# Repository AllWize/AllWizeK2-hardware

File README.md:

# AllWize K2

The AllWize K2 is an Arduino(TM) MKR compatible board based on the SAMD21G microchip and a RadioCrafts RC1701HP module.

Resources:

* [AllWize K2 Wiki Page](http://wiki.allwize.io/index.php?title=Allwize_K2)
* [AllWize Boards](https://github.com/AllWize/allwize-boards) to support the AllWize K2 board from the Arduino IDE and PlatformIO
* [AllWize Library](https://github.com/AllWize/allwize) that supports the RC1701HP radio module.

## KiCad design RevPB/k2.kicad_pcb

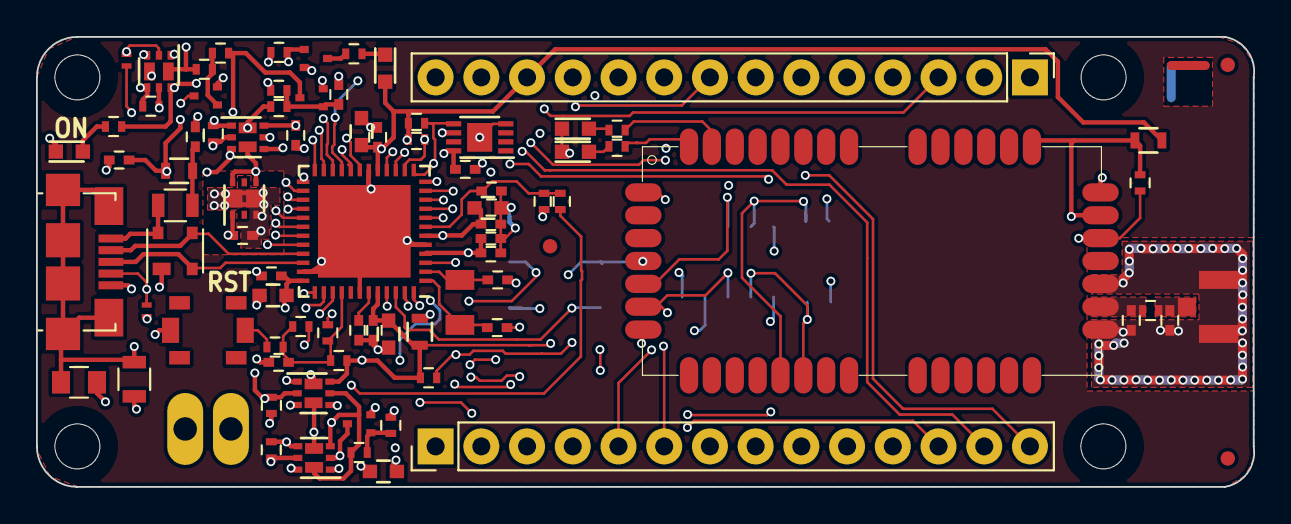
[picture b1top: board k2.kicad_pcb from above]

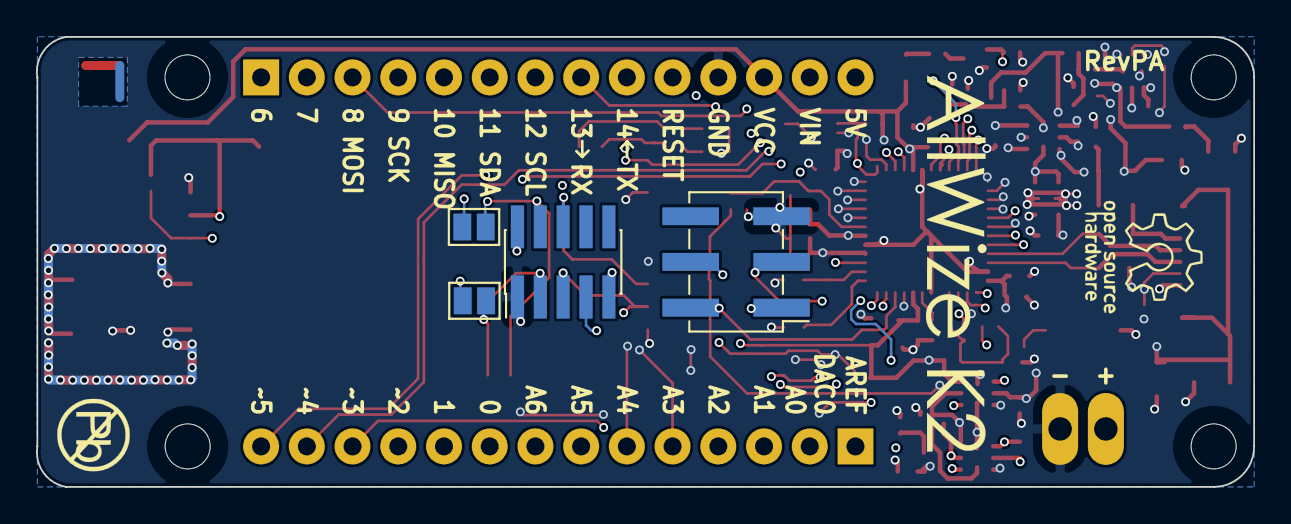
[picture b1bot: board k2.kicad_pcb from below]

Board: 4 copper layers, 67.6 x 25.0 mm, 96 parts (7 on the bottom side), 75 nets.

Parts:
C1: 4n7; C_0805
C2: 10n; C_0402
C3, C4, C5, C8, C9, C10, C16, C17, C20, C21: 100n; C_0402
C6: 4u7; C_0402
C7, C15, C19, C22, C23: 10u; C_0603
C11, C12: 20p; C_0402
C13, C14, C18: 1u; C_0402
C24, C25: 12p; C_0402
D1, D2, D5, D7: LED-DIODE; LED_0603
D3: PRTR5V0U2X; SOT-143
D4, D6: PMEG2005EL; SOD-882
FD1, FD2, FD3: FIDUCIAL; FIDUCIAL-08
G1: LOGO; allwize-k2-logo
G3: OSH; osh
G4: PB_FREE; Pb-free
J1: USB_B_Micro; USB_Micro-B_ZX62-AB-5PA_31
J2: Conn_01x02; OSTVN02
J3: Conn_02x05_Odd_Even; PinHeader_2x05_P1.27mm_Vertical_SMD
J4: Conn_Coaxial_uFL; uFL-CONN
J5: Conn_02x03_Odd_Even; PinHeader_2x03_P2.54mm_Vertical_SMD
J6, J7: Conn_01x14; PinHeader_1x14_P2.54mm_Vertical
J15, J16, J21, J22: NPTH-HOLE; HOLE_2.5MM
JP1, JP2: SolderJumper_2_Open; SolderJumper-2_P1.3mm_Open_Pad1.0x1.5mm
L1, L2, L3: Ferrite_Bead; R_0603
L4: 20n; R_0402
Q1, Q2, Q5, Q8: 2N7002T; SOT-523-3
Q3, Q4, Q6, Q7: DMP2065UFDB; U-DFN2020-6
R1: 1M; R_0805
R2, R3, R14, R24: 1k; R_0402
R4, R26, R27: 4k7; R_0402
R5: PTC; R_0805
R6, R7, R8, R16, R23: 100k; R_0402
R9, R18, R20, R21: 330R; R_0402
R10: 680k; R_0402
R11: 330k; R_0402
R12, R13, R17, R19, R22, R25: 10k; R_0402
R15: 47k; R_0402
SW1: PUSHBUTTON; PTS8020
U1: ECC508A; UDFN-8-1EP_3x2mm_P0.5mm_EP1.4x1.6mm
U2: RC1701xx-MBUS
U3: SAMD21G18; QFN-48-1EP_7x7mm_P0.5mm_EP5.15x5.15mm
U4: TLV757P; WSON-6
Y1: 32768Hz; ABS07-32768Hz

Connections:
+3.3V: C4.1, C15.1, C16.1, C17.1, C19.1, C20.1, C22.1, C23.1, D7.2, J5.1, J7.12, L1.1, L3.1, Q6.6, Q6.8, Q7.6, Q7.8, R17.2, R25.1, R26.2, R27.2, U1.8, U3.17, U3.36, U3.44
+5V: C13.1, J7.14, Q3.6, Q3.8, Q4.6, Q4.8, R14.2, U4.4, U4.6
/0: J6.9, U3.31
/1: J6.10, U3.32
/6: J7.1, Q8.1, R23.2, U3.29
/7: J7.2, U3.30
/A1: J6.3, U3.47
/A2: J6.4, U3.48
/A3: J6.5, U3.9
/A4: J6.6, U3.10
/A5: J6.7, U3.11
/A6: J6.8, U3.12
/AN_3V3: C7.1, C10.1, L3.2, U3.6
/AREF: C6.1, C8.1, J6.1, U3.4
/DAC0/A0: J6.2, U3.3
/MISO: J7.5, U3.28
/MOSI: J7.3, U3.25
/RC_CFG: U2.4, U3.8
/RC_DC: J3.3, JP2.2, U2.20
/RC_DD: J3.4, JP1.2, U2.19
/RC_RX: J3.5, U2.6, U3.21
/RC_TX: J3.6, U2.5, U3.24
/RC_VCC: J3.2, J3.9, L1.2, R4.2, U2.13, U2.41
/RX: J7.8, U3.38
/SCK: J7.4, U3.26
/SCL: J7.7, R26.1, U1.6, U3.14
/SDA: J7.6, R27.1, U1.5, U3.13
/SWCLK: J5.4, R25.2, U3.45
/SWDIO: J5.2, U3.46
/TX: J7.9, U3.37
/USB_D+: D3.2, J1.3, U3.34
/USB_D-: D3.3, J1.2, U3.33
/USB_ID: D4.2, D6.2, J1.4
/VBAT: J2.1, Q7.3, Q7.7, R10.2
/~RC_RESET~: J3.7, R4.1, U2.12, U3.39
/~RESET~: J7.10, R21.2
/~~2: J6.11, U3.15
/~~3: J6.12, U3.16
/~~4: J6.13, U3.19
/~~5: J6.14, U3.20
GND: C1.2, C2.2, C3.2, C4.2, C5.2, C6.2, C7.2, C8.2, C9.2, C10.2, C11.2, C12.2, C13.2, C14.1, C15.2, C16.2, C17.2, C18.2, C19.2, C20.2, C21.2, C22.2, C23.2, C24.2, C25.2, D1.1, D2.1, D5.1, J1.5, J2.2, J3.1, J4.1, J4.3, J5.5, J7.11, Q1.2, Q2.2, Q5.2, Q8.2, R1.1, R7.1, R11.1, R16.1, R19.1, R23.1, SW1.2, U1.4, U1.9, U2.1, U2.7, U2.8, U2.10, U2.14, U3.5, U3.18, U3.35, U3.42, U3.49, U4.3, U4.7
unnamed: C1.1, D3.1, J1.6, R1.2
unnamed: C2.1, L2.2, R5.1
unnamed: C5.1, Q2.1, R6.1, R7.2
unnamed: C9.1, R10.1, R11.2, U3.7
unnamed: C11.1, U3.1, Y1.1
unnamed: C12.1, U3.2, Y1.2
unnamed: C14.2, U3.43
unnamed: C18.1, Q6.3, Q6.7, Q7.2, Q7.5, R15.2, R19.2, U4.1
unnamed: C21.1, R17.1, R18.1, R20.1, R21.1, U3.40
unnamed: C24.1, L4.1, U2.9
unnamed: C25.1, J4.2, L4.2
unnamed: D1.2, R2.1
unnamed: D2.2, R3.1
unnamed: D3.4, J1.1, R5.2
unnamed: D4.1, Q1.3, Q3.2, Q3.5, R12.1
unnamed: D5.2, R14.1
unnamed: D6.1, U3.27
unnamed: D7.1, R24.1
unnamed: J5.3, R20.2
unnamed: JP1.1, U3.23
unnamed: JP2.1, U3.22
unnamed: Q1.1, R8.1, R9.2
unnamed: Q2.3, Q4.2, Q4.5, R9.1, R13.1
unnamed: Q3.1, Q3.4, R12.2
unnamed: Q4.1, Q4.4, R13.2
unnamed: Q5.1, R15.1, R16.2
unnamed: Q5.3, Q6.2, Q6.5, R22.1
unnamed: Q6.1, Q6.4, R22.2
unnamed: Q7.1, Q7.4
unnamed: Q8.3, R24.2
unnamed: R2.2, U2.30
unnamed: R3.2, U2.29
unnamed: R18.2, SW1.1
VIN: C3.1, J7.13, L2.1, Q3.3, Q3.7, Q4.3, Q4.7, R6.2, R8.2

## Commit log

2018-08-23 First commit
    With just the manufacturing documentation
2019-08-21 Add links to the wiki in the README page
2019-08-21 Fix link to allwize-boards repo
2019-08-26 Adding RevPB
